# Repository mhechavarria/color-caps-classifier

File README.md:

# color-caps-classifier
A project made mostly in python to classifie color caps using OpenCV and Python

Link to video: https://drive.google.com/open?id=1r29vyWqCW7NpwiLaEyCusYoAQh5E9Sr1

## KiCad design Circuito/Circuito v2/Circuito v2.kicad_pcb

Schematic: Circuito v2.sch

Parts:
J1: SENSOR1; TerminalBlock_bornier-3_P5.08mm
R1: 220; R_Axial_DIN0207_L6.3mm_D2.5mm_P7.62mm_Horizontal
R2: 39K; R_Axial_DIN0207_L6.3mm_D2.5mm_P7.62mm_Horizontal
R3: 47K; R_Axial_DIN0207_L6.3mm_D2.5mm_P7.62mm_Horizontal
R4, R6: 10K; R_Axial_DIN0207_L6.3mm_D2.5mm_P7.62mm_Horizontal
R5: 1K6; R_Axial_DIN0207_L6.3mm_D2.5mm_P7.62mm_Horizontal
U1: CNY70; DIP-4_W7.62mm_LongPads
U2: LM324; DIP-14_W7.62mm_LongPads

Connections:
+5V: J1.1, R1.1, R3.1, U1.3, U2.4 (V+)
GND: J1.3, R2.1, R4.2, U1.2, U2.11 (V-)
unnamed: J1.2, R6.2, U2.7
unnamed: R1.2, U1.1
unnamed: R2.2, U1.4, U2.3 (+)
unnamed: R3.2, R4.1, U2.6 (-)
unnamed: R5.1, U2.1, U2.2 (-)
unnamed: R5.2, R6.1, U2.5 (+)

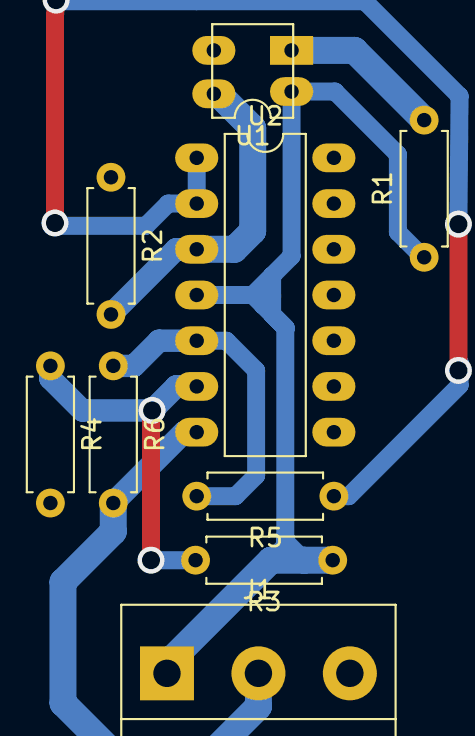
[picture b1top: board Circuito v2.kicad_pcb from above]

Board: 2 copper layers, 9 parts (0 on the bottom side), 8 nets.

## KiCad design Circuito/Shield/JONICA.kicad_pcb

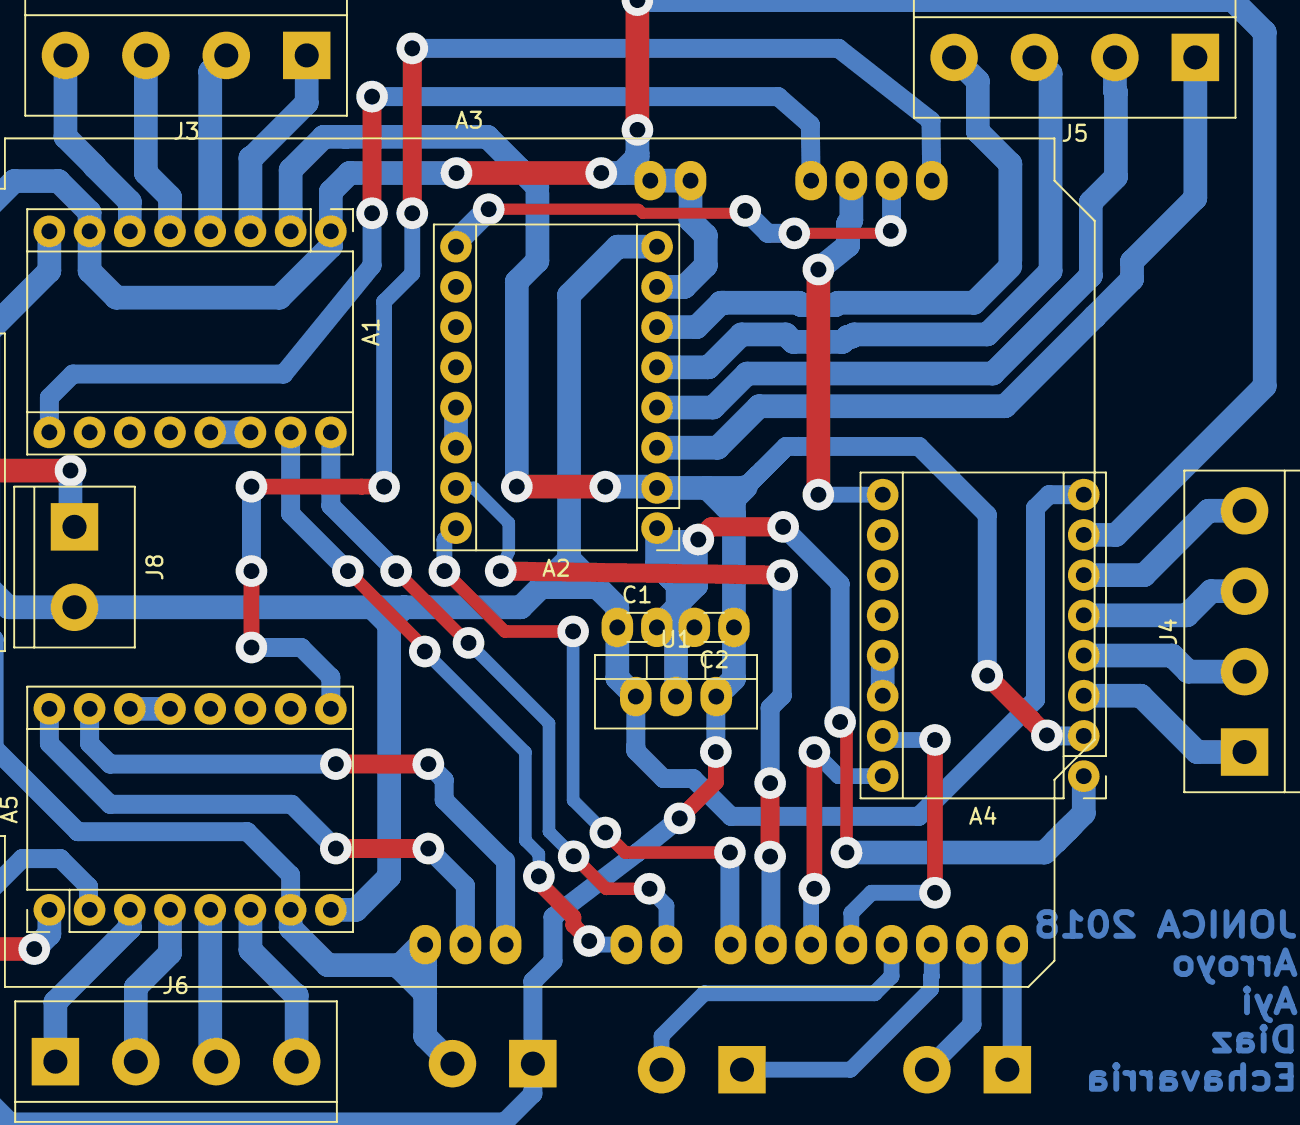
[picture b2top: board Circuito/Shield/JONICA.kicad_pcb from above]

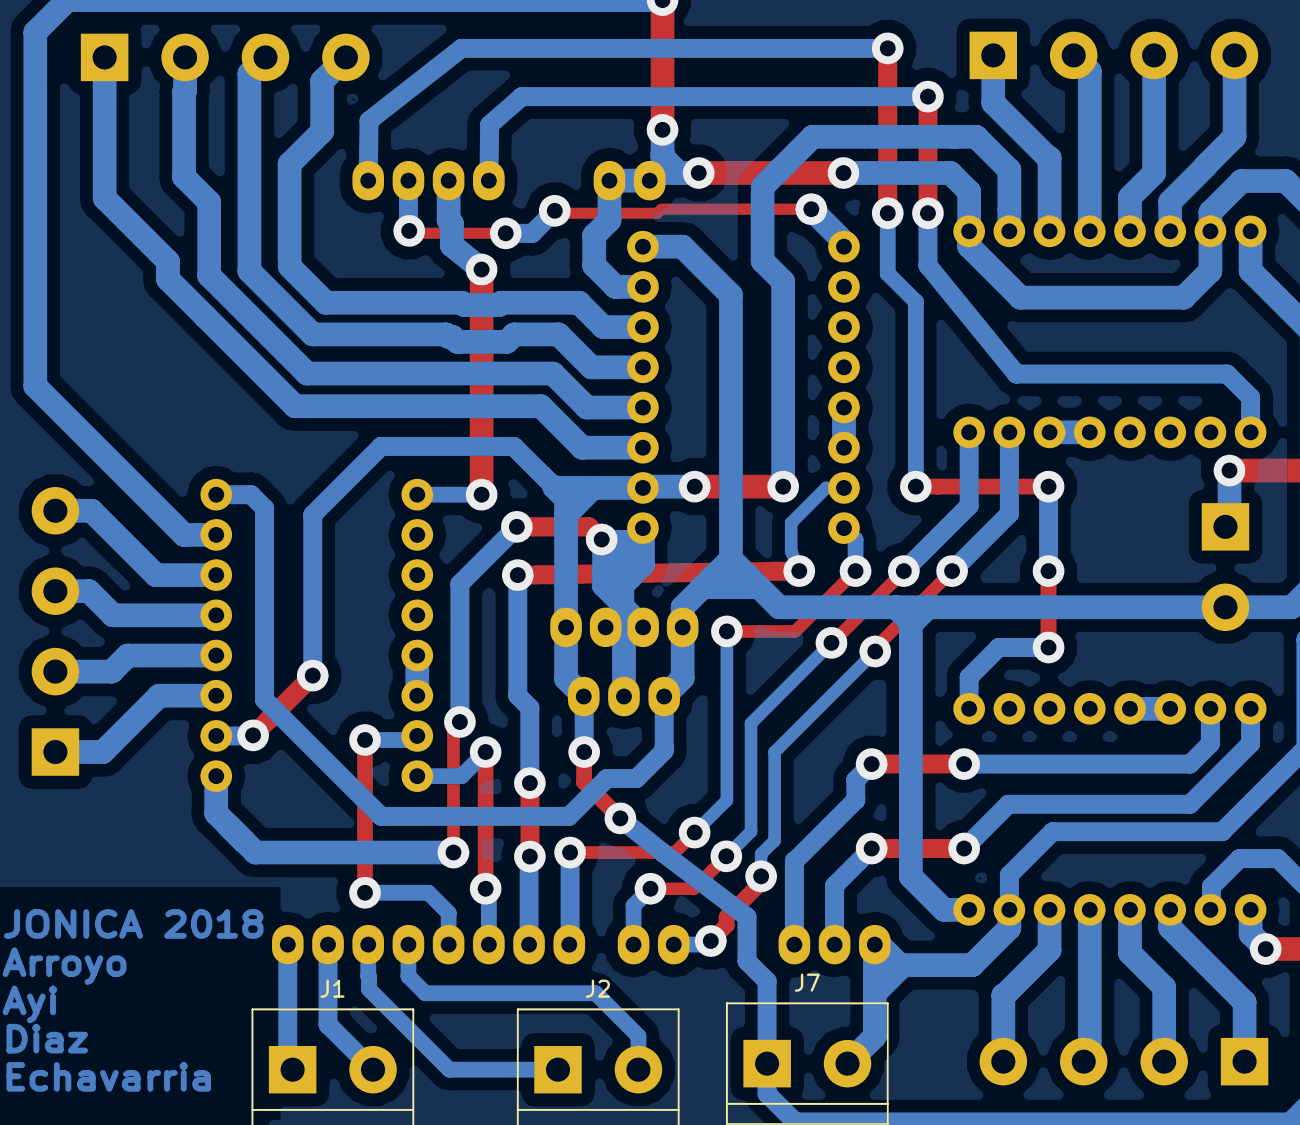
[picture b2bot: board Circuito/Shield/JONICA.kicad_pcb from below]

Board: 2 copper layers, 16 parts (3 on the bottom side), 39 nets.

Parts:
A1, A2, A4, A5: Pololu_Breakout_A4988; Pololu_Breakout-16_15.2x20.3mm
A3: Arduino_UNO_R3
C1: 330nF; C_Disc_D3.0mm_W1.6mm_P2.50mm
C2: 100nF; C_Disc_D3.0mm_W1.6mm_P2.50mm
J1: UART; TerminalBlock_bornier-2_P5.08mm
J2: SENSORES; TerminalBlock_bornier-2_P5.08mm
J3: M1; TerminalBlock_bornier-4_P5.08mm
J4: M2; TerminalBlock_bornier-4_P5.08mm
J5: M3; TerminalBlock_bornier-4_P5.08mm
J6: M0-POLOLU; TerminalBlock_bornier-4_P5.08mm
J7: ALIM_SENSORES; TerminalBlock_bornier-2_P5.08mm
J8: ALIMENTACION; TerminalBlock_bornier-2_P5.08mm
U1: L7805; TO-220-3_Vertical

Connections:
+5V: A1.2, A2.2, A4.2, A5.2, C2.1, J7.1, U1.3
+12V: A1.8, A2.8, A4.8, A5.8, C1.1, J8.2, U1.1
/ENA0-POLOLU: A3.12, A5.9
/ENA1: A1.9, A3.9
/ENA2: A3.10, A4.9
/ENA3: A2.9, A3.11
/M0_1A: A5.3, J6.1
/M0_1B: A5.4, J6.2
/M0_2A: A5.5, J6.3
/M0_2B: A5.6, J6.4
/M0_DIR: A3.28, A5.16
/M0_STEP: A3.27, A5.15
/M1_1A: A1.3, J3.1
/M1_1B: A1.4, J3.2
/M1_2A: A1.5, J3.3
/M1_2B: A1.6, J3.4
/M1_DIR: A1.16, A3.23
/M1_STEP: A1.15, A3.24
/M2_1A: A4.3, J4.1
/M2_1B: A4.4, J4.2
/M2_2A: A4.5, J4.3
/M2_2B: A4.6, J4.4
/M2_DIR: A3.20, A4.16
/M2_STEP: A3.19, A4.15
/M3_1A: A2.3, J5.1
/M3_1B: A2.4, J5.2
/M3_2A: A2.5, J5.3
/M3_2B: A2.6, J5.4
/M3_DIR: A2.16, A3.22
/M3_STEP: A2.15, A3.21
/RX: A3.15, J1.1
/SENSOR1: A3.17, J2.1
/SENSOR2: A3.18, J2.2
/TX: A3.16, J1.2
GND: A1.1, A1.7, A2.1, A2.7, A3.6, A3.7, A3.29, A4.1, A4.7, A5.1, A5.7, C1.2, C2.2, J7.2, J8.1, U1.2
unnamed: A1.13, A1.14
unnamed: A2.13, A2.14
unnamed: A4.13, A4.14
unnamed: A5.13, A5.14

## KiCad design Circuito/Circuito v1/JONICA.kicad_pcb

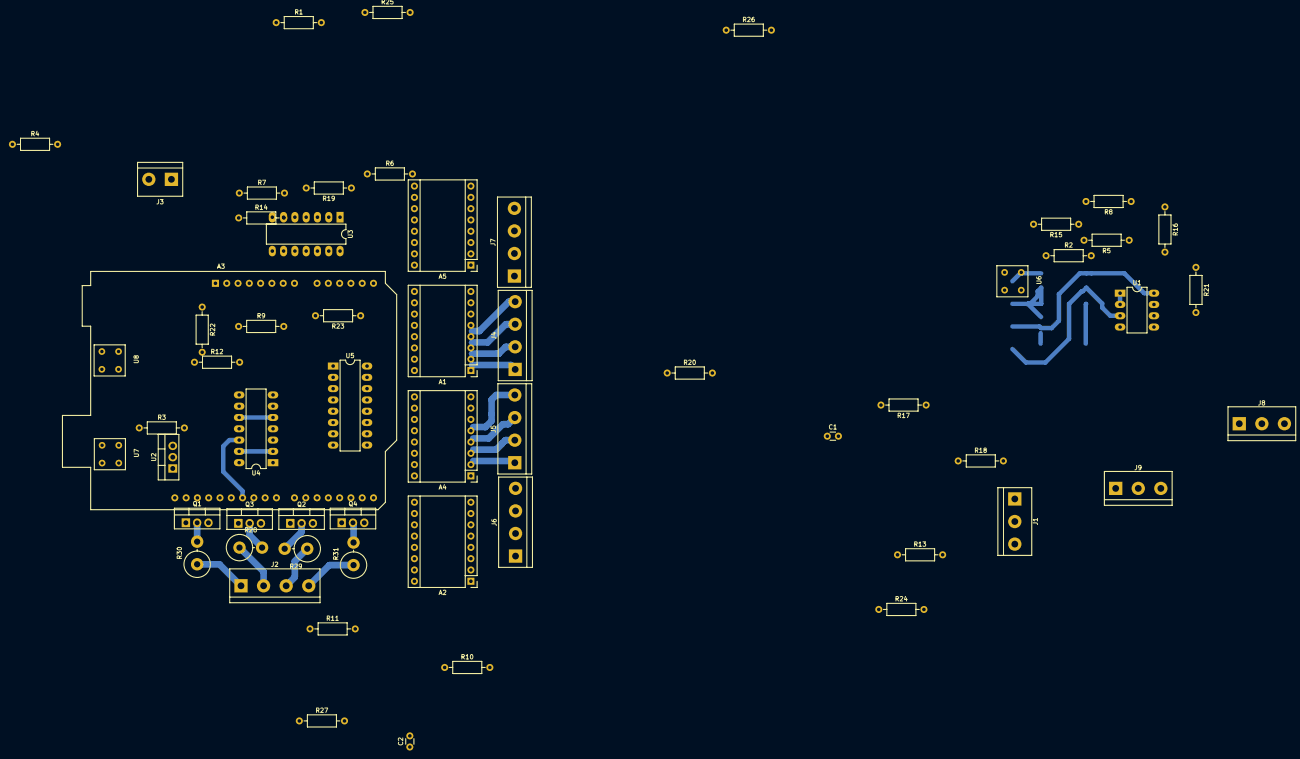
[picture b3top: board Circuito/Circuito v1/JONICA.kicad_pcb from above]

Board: 2 copper layers, 59 parts (0 on the bottom side), 76 nets.

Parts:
A1, A2, A4, A5: Pololu_Breakout_A4988; Pololu_Breakout-16_15.2x20.3mm
A3: Arduino_UNO_R3
C1: 330nF; C_Disc_D3.0mm_W1.6mm_P2.50mm
C2: 100nF; C_Disc_D3.0mm_W1.6mm_P2.50mm
J1: SENSOR3; TerminalBlock_bornier-3_P5.08mm
J2: M0-MOSFET; TerminalBlock_bornier-4_P5.08mm
J3: UART; TerminalBlock_bornier-2_P5.08mm
J4: M1; TerminalBlock_bornier-4_P5.08mm
J5: M2; TerminalBlock_bornier-4_P5.08mm
J6: M3; TerminalBlock_bornier-4_P5.08mm
J7: M0-POLOLU; TerminalBlock_bornier-4_P5.08mm
J8: SENSOR2; TerminalBlock_bornier-3_P5.08mm
J9: SENSOR1; TerminalBlock_bornier-3_P5.08mm
Q1, Q2, Q3, Q4: IRLZ44N; TO-220-3_Vertical
R1, R16, R18, R20, R21, R22, R23: 10k; R_Axial_DIN0207_L6.3mm_D2.5mm_P10.16mm_Horizontal
R2, R3, R4: 220; R_Axial_DIN0207_L6.3mm_D2.5mm_P10.16mm_Horizontal
R5, R6, R7: 39k; R_Axial_DIN0207_L6.3mm_D2.5mm_P10.16mm_Horizontal
R8, R9, R10: 1k6; R_Axial_DIN0207_L6.3mm_D2.5mm_P10.16mm_Horizontal
R11, R13, R24, R26: 1k5; R_Axial_DIN0207_L6.3mm_D2.5mm_P10.16mm_Horizontal
R12, R14, R25, R27: 4k7; R_Axial_DIN0207_L6.3mm_D2.5mm_P10.16mm_Horizontal
R15, R17, R19: 47k; R_Axial_DIN0207_L6.3mm_D2.5mm_P10.16mm_Horizontal
R28, R29, R30, R31: 3.9; R_Axial_DIN0614_L14.3mm_D5.7mm_P5.08mm_Vertical
U1: LM358; DIP-8_W7.62mm_LongPads
U2: L7805; TO-220-3_Vertical
U3: LM324; DIP-14_W7.62mm_LongPads
U4: 74LS08; DIP-14_W7.62mm_LongPads
U5: ULN2003A; DIP-16_W7.62mm_LongPads
U6, U7, U8: CNY70

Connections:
+5V: A1.2, A2.2, A4.2, A5.2, C2.1, J1.1, J8.1, J9.1, R2.2, R3.2, R4.2, R15.2, R17.2, R19.2, U1.8, U2.3, U3.4, U4.14, U6.3, U7.3, U8.3
+12V: A1.8, A2.8, A4.8, A5.8, C1.1, R11.1, R13.1, R24.1, R26.1, U2.1
/ENA0-GATES: A3.12, R1.1, U4.2, U4.5, U4.10, U4.13
/ENA0-POLOLU: A3.13, A5.9
/ENA1: A1.9, A3.9
/ENA2: A3.10, A4.9
/ENA3: A2.9, A3.11
/M0_1A: A5.3, J7.1
/M0_1B: A5.4, J7.2
/M0_2A: A5.5, J7.3
/M0_2B: A5.6, J7.4
/M0_DIR: A3.28, A5.16
/M0_STEP: A3.27, A5.15
/M1_1A: A1.3, J4.1
/M1_1B: A1.4, J4.2
/M1_2A: A1.5, J4.3
/M1_2B: A1.6, J4.4
/M1_DIR: A1.16, A3.18
/M1_STEP: A1.15, A3.17
/M2_1A: A4.3, J5.1
/M2_1B: A4.4, J5.2
/M2_2A: A4.5, J5.3
/M2_2B: A4.6, J5.4
/M2_DIR: A3.20, A4.16
/M2_STEP: A3.19, A4.15
/M3_1A: A2.3, J6.1
/M3_1B: A2.4, J6.2
/M3_2A: A2.5, J6.3
/M3_2B: A2.6, J6.4
/M3_DIR: A2.16, A3.22
/M3_STEP: A2.15, A3.21
/RX: A3.15, J3.1
/TX: A3.16, J3.2
GND: A1.1, A1.7, A2.1, A2.7, A3.6, A3.7, A3.29, A4.1, A4.7, A5.1, A5.7, C1.2, C2.2, J1.3, J8.3, J9.3, Q1.3, Q2.3, Q3.3, Q4.3, R1.2, R5.2, R6.2, R7.2, R12.2, R14.2, R16.1, R18.1, R20.1, R25.2, R27.2, U1.4, U2.2, U3.11, U4.7, U5.8, U6.2, U7.2, U8.2
unnamed: A1.13, A1.14
unnamed: A2.13, A2.14
unnamed: A3.23, U4.1
unnamed: A3.24, U4.4
unnamed: A3.25, U4.9
unnamed: A3.26, U4.12
unnamed: A4.13, A4.14
unnamed: A5.13, A5.14
unnamed: J1.2, R23.1, U3.14
unnamed: J2.1, R30.1
unnamed: J2.2, R28.1
unnamed: J2.3, R29.1
unnamed: J2.4, R31.1
unnamed: J8.2, R22.1, U3.7
unnamed: J9.2, R21.1, U1.7
unnamed: Q1.1, R11.2, R12.1, U5.16
unnamed: Q1.2, R30.2
unnamed: Q2.1, R13.2, R14.1, U5.14
unnamed: Q2.2, R29.2
unnamed: Q3.1, R24.2, R25.1, U5.15
unnamed: Q3.2, R28.2
unnamed: Q4.1, R26.2, R27.1, U5.13
unnamed: Q4.2, R31.2
unnamed: R2.1, U6.1
unnamed: R3.1, U7.1
unnamed: R4.1, U8.1
unnamed: R5.1, U1.3, U6.4
unnamed: R6.1, U3.3, U7.4
unnamed: R7.1, U3.10, U8.4
unnamed: R8.2, U1.1, U1.2
unnamed: R9.2, U3.1, U3.2
unnamed: R10.1, R23.2, U3.12
unnamed: R10.2, U3.8, U3.9
unnamed: R15.1, R16.2, U1.6
unnamed: R17.1, R18.2, U3.6
unnamed: R19.1, R20.2, U3.13
unnamed: R8.1, R21.2, U1.5
unnamed: R9.1, R22.2, U3.5
unnamed: U4.3, U5.1
unnamed: U4.6, U5.2
unnamed: U4.8, U5.3
unnamed: U4.11, U5.4
